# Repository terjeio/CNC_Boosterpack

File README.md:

## CNC BoosterPack for Texas Instruments LaunchPads

A BoosterPack that provides 3-axis motor support for some LaunchPads, driver code for [grblHAL](https://github.com/grblHAL) is available for [MSP432P401R](https://github.com/grblHAL/MSP432P401R), [MSP432E401Y](https://github.com/grblHAL/MSP432E401Y), Tiva C\([EK-TM4C123GXL](https://github.com/grblHAL/TM4C123) and [EK-TM4C1294XL](https://github.com/grblHAL/TM4C1294)\) and [MSP430F5529](https://github.com/grblHAL/MSP430F5529).

Prototype "motherboards" has been made for ESP32, STM32F103 \(Bluepill\) and SAMD21 \(MKRZERO\) development boards allowing the CNC BoosterPack to be used with these, I may add them later.

**NOTE:** design files are in [KiCad 5](http://www.kicad.org/) format!

**Features:**

* 3-axis motor support with separate enable for Z and X,Y \(X,Y has a single enable signal\). Trinamic version has separate enable for all axes.

* On-board sockets for Polulu style motor driver modules (A4998 and DRV8825). Separate version for Trinamic drivers \(initially TMC2130\).

* Opto-coupled limit and signal inputs (X, Y, Z, Probe, Reset, Door, Feed Hold and Cycle Start) with 5V drive voltage.

* Opto-coupled signal outputs \(Spindle on, Spindle direction, Flood and Mist\) with jumper selectable drive voltage \(5V internal or externally supplied\). Outputs are open drain \(2N7002\) capable of draining 200mA \(up to 300mA depending on 2N7002 variant\), enough to drive most relays directly. Outputs can be made opto-isolated via jumper settings.

* PWM output for spindle speed control, unbuffered.

* One I2C port with jumper selectable drive voltage \(3.3V or 5V\). This is complemented with a GPIO pin that may be used as an interrupt source, eg. for a I2C-based keypad.

* Two GPIO ports, one with four pins and one with two. Two-pin GPIO-port may be used as secondary UART input, eg. for MPG control.

* Optional on-board EEPROM for persistent storage of settings.

Separate version for Trinamic TMC2130 drivers added, onboard I2C \<\> SPI bridge for driver control. 4-layer board.
A small batch of the Trinamic version has been made, good progress made on [I2C \<\> SPI bridge firmware](https://github.com/terjeio/Trinamic_TMC2130_I2C_SPI_Bridge). Driver monitoring has been delegated to the bridge prosessor, a couple of additional datagrams will be implemented to facilitate support for this in the grblHAL-driver - first out will be for MSP432.

Both designs are now reduced in size so two boards may be mounted on TMC129 or MSP432E401Y LaunchPads for controlling up to 6-axes. 

I have a few bare boards for sale at cost if anyone is interested. The "standard - non-Trinamic" boards I have available is the larger revision 1.0. 

Detailed documentation to follow.

---

## Bonus design: Polulu style motor driver "dummy"

* with buffered \(open drain\) outputs for external drivers like DQ542MA.

**NOTE:** output signals are inverted

---

## Bonus design II: BLDC Motor driver board, 3.3V (or 5V) PWM to 0 - 10V DC conversion

* with opto-coupled PWM input.

* PCB layout matches WSS55 BLDC Driver connector

---
2021-10-28

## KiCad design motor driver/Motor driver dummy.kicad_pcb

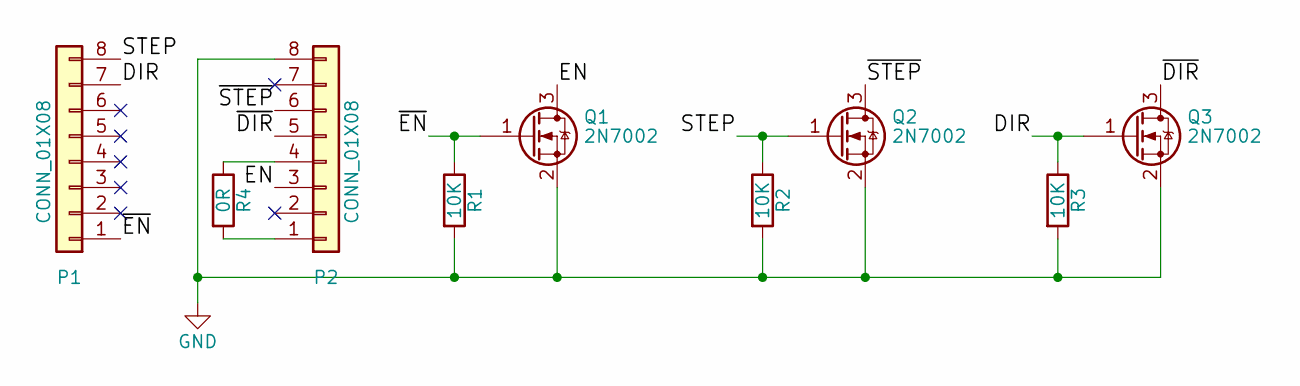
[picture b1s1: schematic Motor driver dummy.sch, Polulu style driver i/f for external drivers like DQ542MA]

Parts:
P1, P2: CONN_01X08; PinHeader_1x08_P2.54mm_Vertical
Q1, Q2, Q3: 2N7002; SOT-23
R1, R2, R3: 10K; R_0805_2012Metric
R4: 0R; R_0805_2012Metric

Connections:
/DIR: P1.7, Q3.1 (G), R3.1
/EN: P2.3, Q1.3 (D)
/STEP: P1.8, Q2.1 (G), R2.1
/~DIR: P2.5, Q3.3 (D)
/~EN: P1.1, Q1.1 (G), R1.1
/~STEP: P2.6, Q2.3 (D)
GND: P2.8, Q1.2 (S), Q2.2 (S), Q3.2 (S), R1.2, R2.2, R3.2
unnamed: P2.1, R4.2
unnamed: P2.4, R4.1

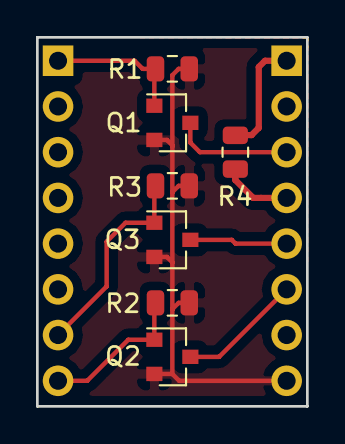
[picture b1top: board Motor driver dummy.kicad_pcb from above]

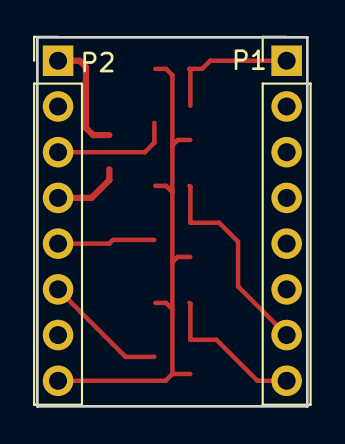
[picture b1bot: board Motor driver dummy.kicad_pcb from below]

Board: 2 copper layers, 15.0 x 20.5 mm, 9 parts (2 on the bottom side), 9 nets.

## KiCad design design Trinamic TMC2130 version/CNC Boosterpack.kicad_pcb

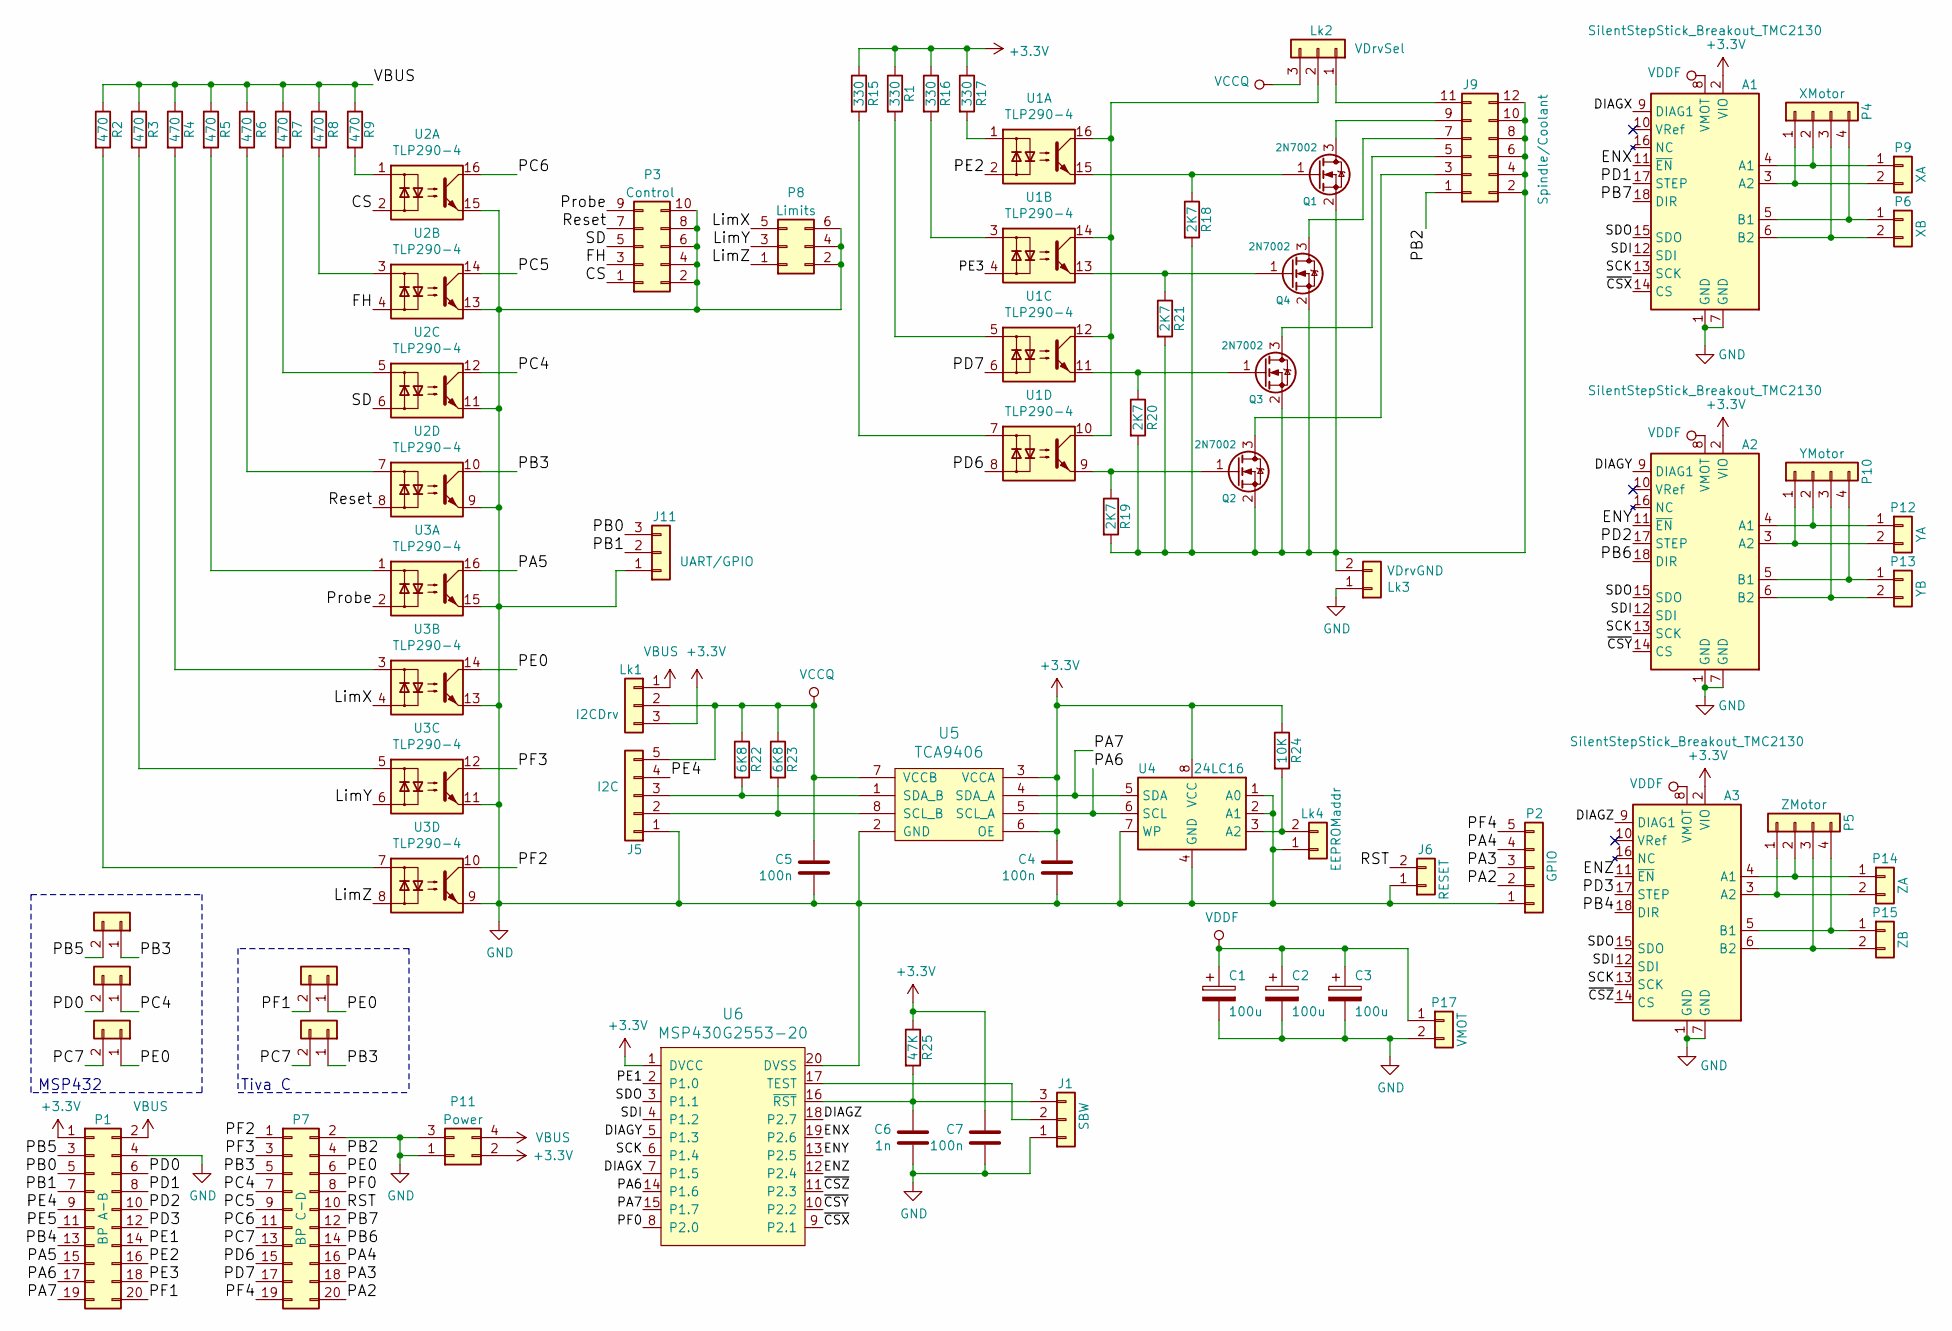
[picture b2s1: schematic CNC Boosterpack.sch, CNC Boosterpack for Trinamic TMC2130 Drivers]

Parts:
A1, A2, A3: SilentStepStick_Breakout_TMC2130; SilentStepStick_TMC2130
C1, C2, C3: 100u; CP_Radial_D8.0mm_P3.50mm
C4, C5, C7: 100n; C_0805_2012Metric
C6: 1n; C_0805_2012Metric
J1: SBW; PinHeader_1x03_P2.54mm_Horizontal
J2, J3, J12, J13, J14: Lk; SolderJumper-2_P1.3mm_Open_RoundedPad1.0x1.5mm
J5: I2C; PinHeader_1x05_P2.54mm_Vertical
J6: RESET; PinHeader_1x02_P2.54mm_Vertical
J9: Spindle/Coolant; PinHeader_2x06_P2.54mm_Vertical
J11: UART/GPIO; PinHeader_1x03_P2.54mm_Vertical
Lk1: I2CDrv; PinHeader_1x03_P2.54mm_Vertical
Lk2: VDrvSel; PinHeader_1x03_P2.54mm_Vertical
Lk3: VDrvGND; PinHeader_1x02_P2.54mm_Vertical
Lk4: EEPROMaddr; SolderJumper-2_P1.3mm_Open_RoundedPad1.0x1.5mm
P1: BP A-B; PinSocket_2x10_P2.54mm_Vertical
P2: GPIO; PinHeader_1x05_P2.54mm_Vertical
P3: Control; PinHeader_2x05_P2.54mm_Vertical
P4: XMotor; PinHeader_1x04_P2.54mm_Vertical_Motor
P5: ZMotor; PinHeader_1x04_P2.54mm_Vertical_Motor
P6: XB; CONN_PWR_2P_3.5MM_CAMBLOCK
P7: BP C-D; PinSocket_2x10_P2.54mm_Vertical
P8: Limits; PinHeader_2x03_P2.54mm_Vertical
P9: XA; CONN_PWR_2P_3.5MM_CAMBLOCK
P10: YMotor; PinHeader_1x04_P2.54mm_Vertical_Motor
P11: Power; PinHeader_2x02_P2.54mm_Vertical
P12: YA; CONN_PWR_2P_3.5MM_CAMBLOCK
P13: YB; CONN_PWR_2P_3.5MM_CAMBLOCK
P14: ZA; CONN_PWR_2P_3.5MM_CAMBLOCK
P15: ZB; CONN_PWR_2P_3.5MM_CAMBLOCK
P17: VMOT; CONN_PWR_2P_3.5MM_CAMBLOCK
Q1, Q2, Q3, Q4: 2N7002; SOT-23
R1, R15, R16, R17: 330; R_0805_2012Metric
R2, R3, R4, R5, R6, R7, R8, R9: 470; R_0805_2012Metric
R18, R19, R20, R21: 2K7; R_0805_2012Metric
R22, R23: 6K8; R_0805_2012Metric
R24: 10K; R_0805_2012Metric
R25: 47K; R_0805_2012Metric
U1, U2, U3: TLP290-4; SOP-16_4.4x10.4mm_P1.27mm
U4: 24LC16; SOIC-8_3.9x4.9mm_P1.27mm
U5: TCA9406; SSOP-8_2.95x2.8mm_P0.65mm
U6: MSP430G2553-20; TSSOP-20_4.4x6.5mm_P0.65mm

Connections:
+3V3: A1.2 (VIO), A2.2 (VIO), A3.2 (VIO), C4.1, C7.1, Lk1.3, P1.1, P11.2, R1.1, R15.1, R16.1, R17.1, R24.1, R25.1, U4.8 (VCC), U5.3 (VCCA), U5.6 (OE), U6.1 (DVCC)
/CS: P3.1, U2.2
/DIAGX: A1.9 (DIAG1), U6.7 (P1.5)
/DIAGY: A2.9 (DIAG1), U6.5 (P1.3)
/DIAGZ: A3.9 (DIAG1), U6.18 (P2.7)
/ENX: A1.11 (~EN), U6.19 (P2.6)
/ENY: A2.11 (~EN), U6.13 (P2.5)
/ENZ: A3.11 (~EN), U6.12 (P2.4)
/FH: P3.3, U2.4
/LimX: P8.5, U3.4
/LimY: P8.3, U3.6
/LimZ: P8.1, U3.8
/PA2: P2.2, P7.20
/PA3: P2.3, P7.18
/PA4: P2.4, P7.16
/PA5: P1.15, U3.16
/PA6: P1.17, U4.6 (SCL), U5.5 (SCL_A), U6.14 (P1.6)
/PA7: P1.19, U4.5 (SDA), U5.4 (SDA_A), U6.15 (P1.7)
/PB0: J11.3, P1.5
/PB1: J11.2, P1.7
/PB2: J9.1, P7.4
/PB3: J2.1, J14.1, P7.5, U2.10
/PB4: A3.18 (DIR), P1.13
/PB5: J2.2, P1.3
/PB6: A2.18 (DIR), P7.14
/PB7: A1.18 (DIR), P7.12
/PC4: J3.1, P7.7, U2.12
/PC5: P7.9, U2.14
/PC6: P7.11, U2.16
/PC7: J12.2, J14.2, P7.13
/PD0: J3.2, P1.6
/PD1: A1.17 (STEP), P1.8
/PD2: A2.17 (STEP), P1.10
/PD3: A3.17 (STEP), P1.12
/PD6: P7.15, U1.8
/PD7: P7.17, U1.6
/PE0: J12.1, J13.1, P7.6, U3.14
/PE1: P1.14, U6.2 (P1.0)
/PE2: P1.16, U1.2
/PE3: P1.18, U1.4
/PE4: J5.4, P1.9
/PE5: P1.11
/PF0: P7.8, U6.8 (P2.0)
/PF1: J13.2, P1.20
/PF2: P7.1, U3.10
/PF3: P7.3, U3.12
/PF4: P2.5, P7.19
/Probe: P3.9, U3.2
/RST: J6.2, P7.10
/Reset: P3.7, U2.8
/SCK: A1.13 (SCK), A2.13 (SCK), A3.13 (SCK), U6.6 (P1.4)
/SD: P3.5, U2.6
/SDI: A1.12 (SDI), A2.12 (SDI), A3.12 (SDI), U6.4 (P1.2)
/SDO: A1.15 (SDO), A2.15 (SDO), A3.15 (SDO), U6.3 (P1.1)
/~CSX: A1.14 (CS), U6.9 (P2.1)
/~CSY: A2.14 (CS), U6.10 (P2.2)
/~CSZ: A3.14 (CS), U6.11 (P2.3)
GND: A1.1 (GND), A1.7 (GND), A2.1 (GND), A2.7 (GND), A3.1 (GND), A3.7 (GND), C1.2, C2.2, C3.2, C4.2, C5.2, C6.2, C7.2, J1.1, J5.1, J6.1, J11.1, Lk3.1, Lk4.1, P1.4, P2.1, P3.2, P3.4, P3.6, P3.8, P3.10, P7.2, P8.2, P8.4, P8.6, P11.1, P11.3, P17.2, U2.9, U2.11, U2.13, U2.15, U3.9, U3.11, U3.13, U3.15, U4.1 (A0), U4.2 (A1), U4.4 (GND), U4.7 (WP), U5.2 (GND), U6.20 (DVSS)
unnamed: A1.3 (A2), P4.1, P9.2
unnamed: A1.4 (A1), P4.2, P9.1
unnamed: A1.5 (B1), P4.4, P6.1
unnamed: A1.6 (B2), P4.3, P6.2
unnamed: A2.3 (A2), P10.1, P12.2
unnamed: A2.4 (A1), P10.2, P12.1
unnamed: A2.5 (B1), P10.4, P13.1
unnamed: A2.6 (B2), P10.3, P13.2
unnamed: A3.3 (A2), P5.1, P14.2
unnamed: A3.4 (A1), P5.2, P14.1
unnamed: A3.5 (B1), P5.4, P15.1
unnamed: A3.6 (B2), P5.3, P15.2
unnamed: C6.1, J1.3, R25.2, U6.16 (~RST~)
unnamed: J1.2, U6.17 (TEST)
unnamed: J5.2, R23.2, U5.8 (SCL_B)
unnamed: J5.3, R22.2, U5.1 (SDA_B)
unnamed: J9.3, Q2.3 (D)
unnamed: J9.5, Q3.3 (D)
unnamed: J9.7, Q4.3 (D)
unnamed: J9.9, Q1.3 (D)
unnamed: J9.2, J9.4, J9.6, J9.8, J9.10, J9.12, Lk3.2, Q1.2 (S), Q2.2 (S), Q3.2 (S), Q4.2 (S), R18.2, R19.2, R20.2, R21.2
unnamed: J9.11, Lk2.1
unnamed: Lk2.2, U1.10, U1.12, U1.14, U1.16
unnamed: Lk4.2, R24.2, U4.3 (A2)
unnamed: Q1.1 (G), R18.1, U1.15
unnamed: Q2.1 (G), R19.1, U1.9
unnamed: Q3.1 (G), R20.1, U1.11
unnamed: Q4.1 (G), R21.1, U1.13
unnamed: R1.2, U1.5
unnamed: R2.2, U3.7
unnamed: R3.2, U3.5
unnamed: R4.2, U3.3
unnamed: R5.2, U3.1
unnamed: R6.2, U2.7
unnamed: R7.2, U2.5
unnamed: R8.2, U2.3
unnamed: R9.2, U2.1
unnamed: R15.2, U1.7
unnamed: R16.2, U1.3
unnamed: R17.2, U1.1
VBUS: Lk1.1, P1.2, P11.4, R2.1, R3.1, R4.1, R5.1, R6.1, R7.1, R8.1, R9.1
VCCQ: C5.1, J5.5, Lk1.2, Lk2.3, R22.1, R23.1, U5.7 (VCCB)
VDDF: A1.8 (VMOT), A2.8 (VMOT), A3.8 (VMOT), C1.1, C2.1, C3.1, P17.1

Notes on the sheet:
MSP432
Tiva C

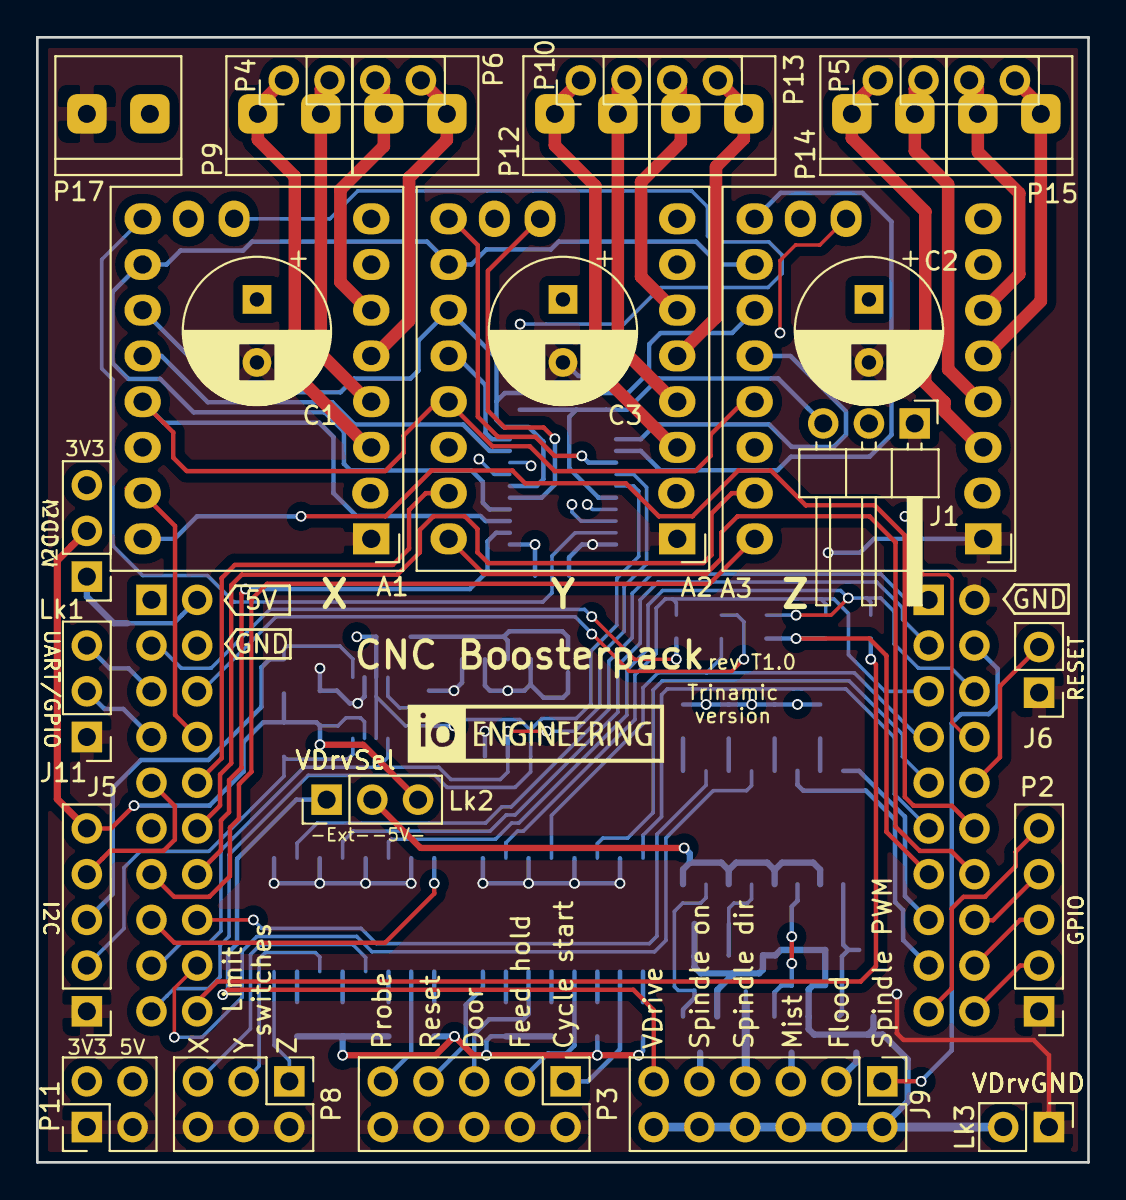
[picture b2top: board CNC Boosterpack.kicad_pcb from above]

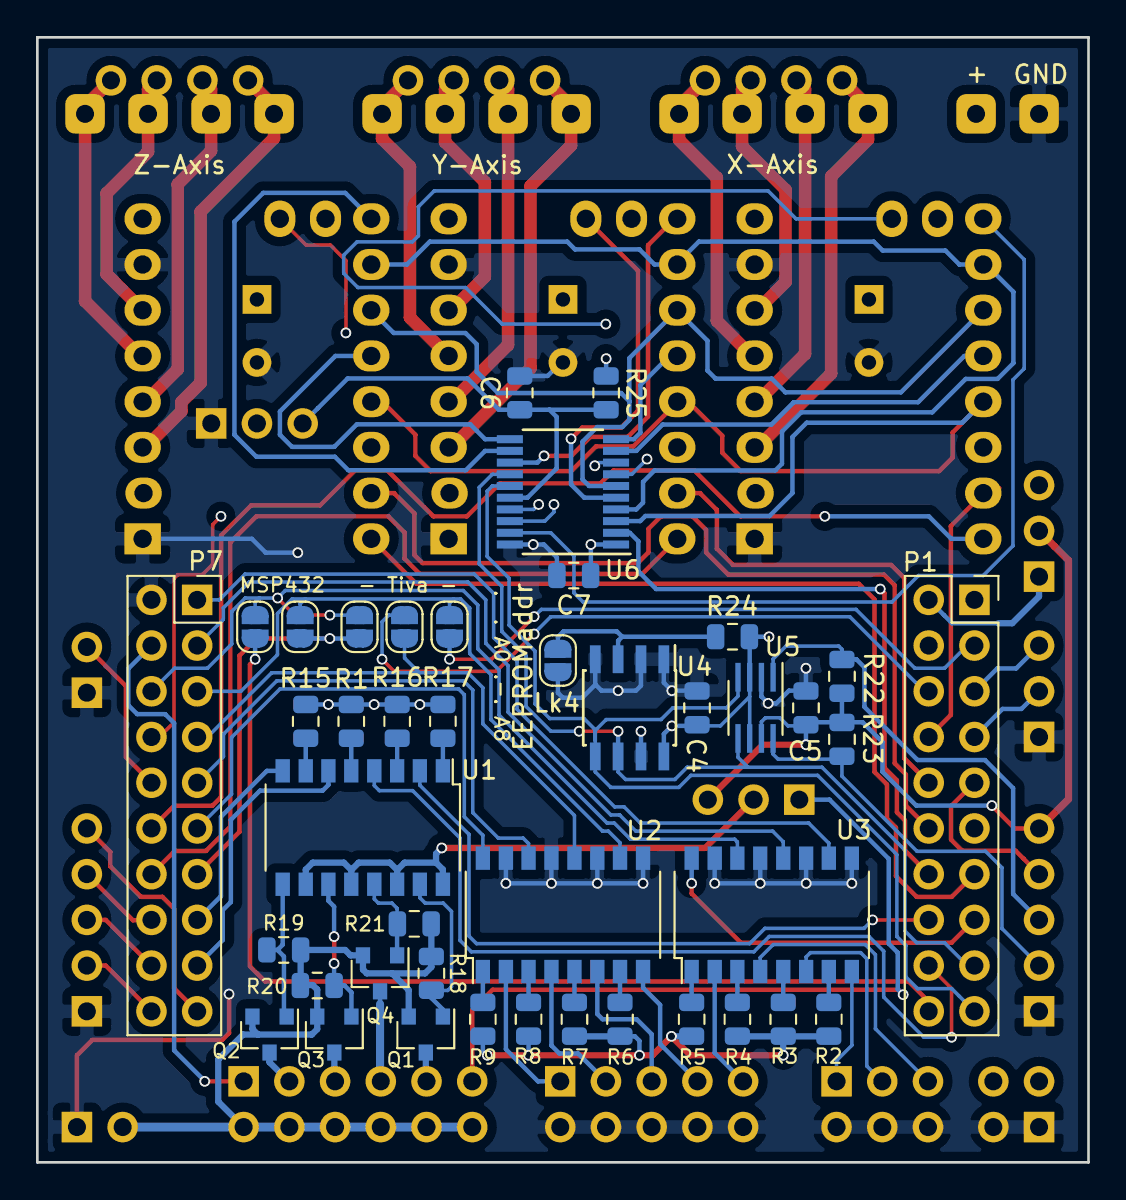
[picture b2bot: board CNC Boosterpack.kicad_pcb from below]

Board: 4 copper layers, 58.4 x 62.5 mm, 70 parts (42 on the bottom side), 100 nets.

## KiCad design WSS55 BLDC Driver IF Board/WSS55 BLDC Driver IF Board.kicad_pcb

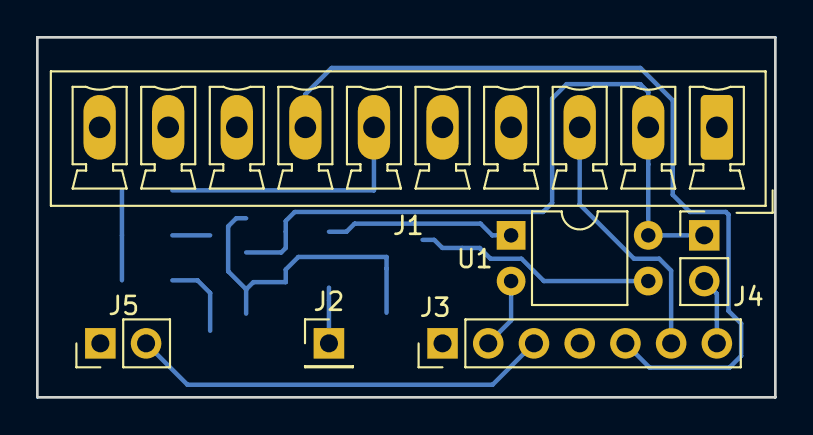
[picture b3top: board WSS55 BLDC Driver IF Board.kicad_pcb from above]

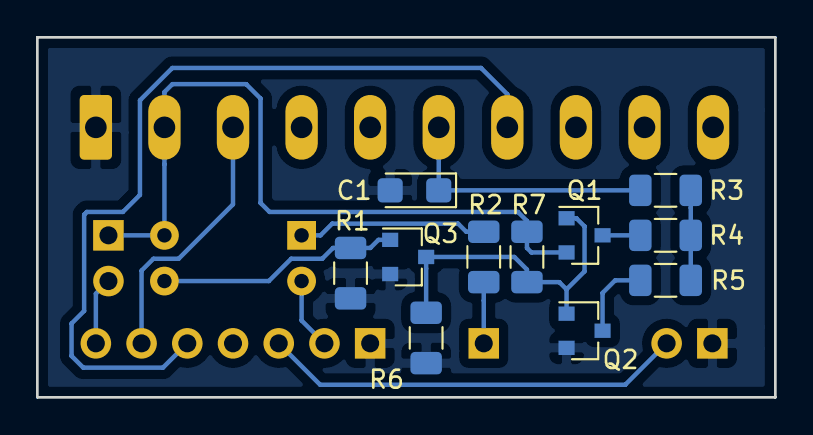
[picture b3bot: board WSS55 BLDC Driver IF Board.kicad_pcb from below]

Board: 2 copper layers, 41.0 x 20.0 mm, 17 parts (11 on the bottom side), 15 nets.

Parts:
C1: 4u7; CP_EIA-3216-10_Kemet-I
J1: BLDC Driver; PhoenixContact_MCV_1,5_10-G-3.81_1x10_P3.81mm_Vertical
J2: 3V3; PinHeader_1x01_P2.54mm_Vertical
J3: CNC Boosterpack out; PinHeader_1x07_P2.54mm_Vertical
J4: VDrive; PinHeader_1x02_P2.54mm_Vertical
J5: Coolant out; PinHeader_1x02_P2.54mm_Vertical
Q1: IRLML6402; SOT-23
Q2, Q3: 2N7002; SOT-23
R1: 270; R_1206_3216Metric
R2, R4, R5: 220; R_1206_3216Metric
R3: 1K2; R_1206_3216Metric
R6: 10K; R_1206_3216Metric
R7: 820; R_1206_3216Metric
U1: PC817; DIP-4_W7.62mm

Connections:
GND: C1.2, J1.1, J3.1, J5.1, Q2.2, Q3.2, R1.1, R6.2
unnamed: C1.1, J1.6, R3.2
unnamed: J1.2, J4.1, Q1.2, R7.1, U1.4
unnamed: J1.3, J3.6
unnamed: J1.7, J3.5
unnamed: J2.1, R2.1
unnamed: J3.2, U1.2
unnamed: J3.3, J5.2
unnamed: J3.7, J4.2
unnamed: Q1.1, Q2.1, Q3.3, R6.1, R7.2
unnamed: Q1.3, R4.1
unnamed: Q2.3, R5.2
unnamed: Q3.1, R1.2, U1.3
unnamed: R2.2, U1.1
unnamed: R3.1, R4.2, R5.1

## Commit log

2018-04-14 :tada: Added .gitattributes & .gitignore files
2018-04-14 CNC Boosterpack desging files
    added files
2018-04-17 Added bonus design
    Motor driver "dummy" for extenal motor drivers
2018-07-26 Added pin assignments
2018-09-02 Updated readme and silk screen
2018-09-20 Reduced PCB size
    Reduced PCB size to enable two boards to be used with the EK-TM4C1294X
    LaunchPad - providing up to 6 axes of control. Update to driver for this
    LauncPad underway to facilitate IP-streaming of jobs.
2018-10-26 Added design for Trinamic TMC2130 drivers.
    On-board I2C <> SPI bridge, 4-layer board.
2018-12-10 Added MSP432E401Y to pinout assignments
    Changed card images to Trinamic TMC2130 version
2019-04-22 Added bonus design for PWM > DC converter
    I am using this to convert a 3.3V PWM spindle signal to 0 - 10V DC for a
    WSS55 BLDC driver. Can be used with 5V PWM signals and other output
    voltages as well. Input is opto-isolated.
2019-07-22 Updated to latest revision
    A small batch of the Trinamic-version PCB has been made, driver
    development in good progress. Marlin-style M-commands will be supported
    including status reports. Grbl protocol extensions allows real-trime
    plotting of data (stallguard value) for simpler tuning.
2021-10-28 Updated motor driver dummy to KiCad v5 format

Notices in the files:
WSS55 BLDC Driver IF Board/WSS55 BLDC Driver IF Board.kicad_pcb:
Licensed under CERN OHL v.1.2 or later
